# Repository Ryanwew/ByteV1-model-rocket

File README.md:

This repo contains all of the design files I used to create an arduino-based flight computer and groud control system.

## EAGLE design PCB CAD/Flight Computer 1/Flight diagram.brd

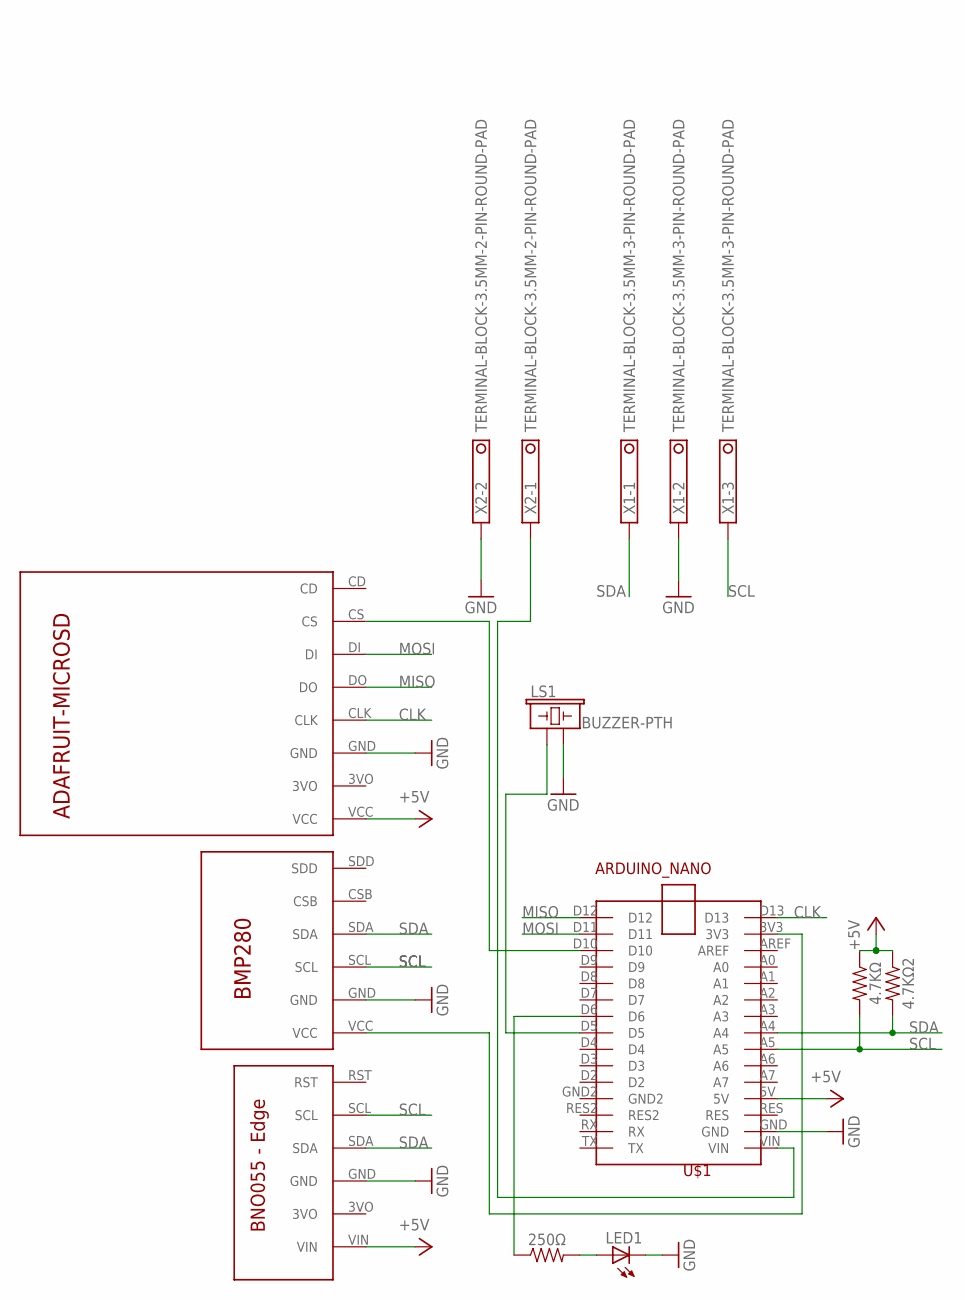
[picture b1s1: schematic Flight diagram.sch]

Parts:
4.7KΩ, 4.7KΩ2, 250Ω: AXIAL-0.3
LED1: LED5MM
LS1: BUZZER-PTH; BUZZER-12MM
U$1: ARDUINO_NANO; ARDUIN_NANO
U$2: BNO055
U$3: ADAFRUIT-MICROSD
U$4: BMP280
X1: TERMINAL-BLOCK-3.5MM-3-PIN-ROUND-PAD; TERMINAL-BLOCK-3-PIN-3.5MM-ROUND-PAD
X2: TERMINAL-BLOCK-3.5MM-2-PIN-ROUND-PAD; TERMINAL-BLOCK-2-PIN-3.5MM-ROUND-PAD

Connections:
+5V: 4.7KΩ.P$1 (1), 4.7KΩ2.P$1 (1), U$1.5V, U$2.VIN, U$3.VCC
CLK: U$1.D13, U$3.CLK
GND: LED1.K (C), LS1.- (2), U$1.GND, U$2.GND, U$3.GND, U$4.GND, X1.2, X2.2
MISO: U$1.D12, U$3.DO
MOSI: U$1.D11, U$3.DI
unnamed: 250Ω.P$2 (2), LED1.A
unnamed: U$1.3V3, U$4.VCC
unnamed: U$1.VIN, X2.1
unnamed: 250Ω.P$1 (1), U$1.D6
unnamed: U$1.D10, U$3.CS
unnamed: LS1.+ (1), U$1.D5
SCL: 4.7KΩ.P$2 (2), U$1.A5, U$2.SCL, U$4.SCL, X1.3
SDA: 4.7KΩ2.P$2 (2), U$1.A4, U$2.SDA, U$4.SDA, X1.1

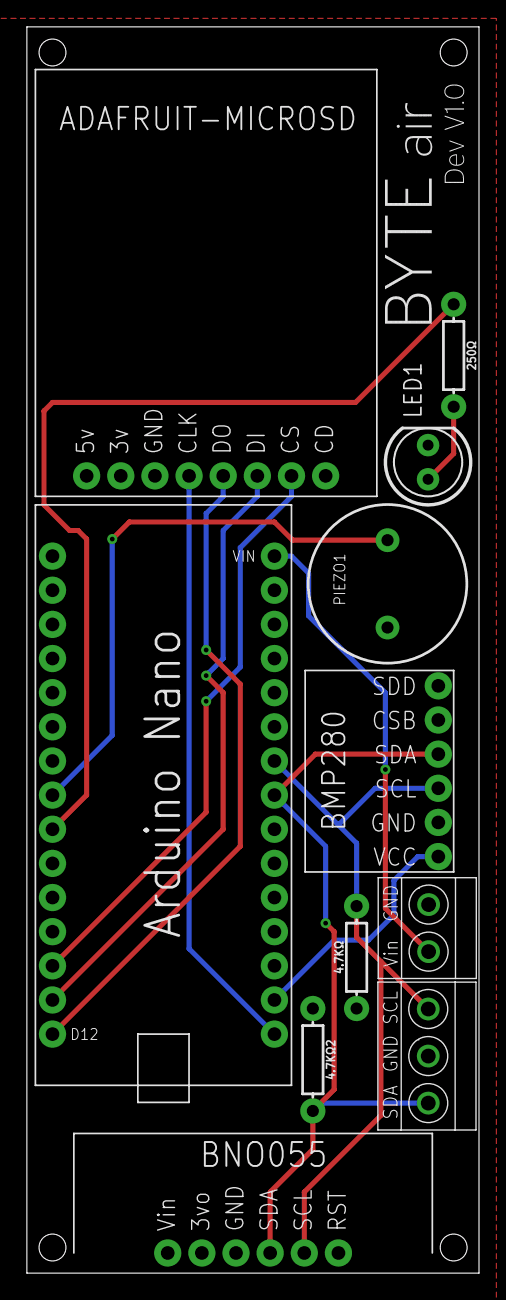
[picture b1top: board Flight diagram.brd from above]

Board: 2 copper layers, 33.6 x 92.7 mm, 11 parts (0 on the bottom side), 13 nets.

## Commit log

2020-06-25 First files
    2 initial testing files
2020-06-27 EAGLE Devices
    Arduino is premade, BNO is a custom-designed simplified library.
2020-06-27 New library
    Custom RoboJax BMP280 EAGLE library
2020-06-27 New library
    Custom simplified library for Aadafruit microSD breakout.
2020-06-29 Edge BNO055
    Version of BNO055 that sits on the edge of the PCB
2020-12-20 Added PCB CAD
2020-12-21 Removed Excess Files
2021-01-17 Added BoM and photo
2021-03-29 Code Re-distribution
2021-03-31 Serial rocket to station communication, added "capture" command
2021-03-31 adding i2c check, added bluetooth validation for GS
2021-04-01 File division
2021-04-02 Shift Register using OOP
2021-04-02 Redid control code with OOP
2021-04-03 code sync
2021-04-03 Program Variations
2021-04-04 MVC Attained
2021-04-04 Byte overflow error fixed, system working
2021-04-06 Serial data validation, file shifting
2021-04-06 Data validation testing
2021-04-06 Validation issue fixed
2021-04-07 Station OOP
2021-04-11 StationOOP proto finished
2021-04-11 OR error management
2021-04-14 Station OOP MVC search
2021-04-15 Returning to original station I2C
2021-04-16 Fixing I2c bus
2021-04-23 I2c error fixed, StationOOP working
2021-04-24 SD testing
2021-04-26 Begun SD conversion to binary files
2021-04-27 floating point testing
2021-04-27 Added .dat evaluation
2021-04-27 Multibyte parsing
2021-04-27 CSV export
2021-04-27 Finished test parse app
2021-04-27 Remade URP for serialized data
2021-04-28 BNO isolation
2021-04-28 Revised isolated BMP
2021-04-28 isolated BMP written
2021-04-30 Started RocketOOP
2021-05-01 Base RocketOOP
2021-05-02 Transferring sensor actions to function
2021-05-08 Finished RocketOOP first prototype
2021-05-16 RocketOOP troubleshooting
2021-05-16 Corrected full loop failure
2021-05-17 data conversion gui
2021-05-17 GUI Implemented for data conversion
2021-05-17 reformatted converter for RocketOOP
2021-05-18 added simulation
2021-05-19 Created fairing, improved simulation
2021-05-20 Updated fairing
2021-05-22 Begun station schematic
2021-05-26 shift issue isolated
2021-05-27 Fixing serial state issues
2021-05-28 debugging shift class
2021-05-28 fixed shift register issues, added continuity detection to station
2021-05-30 12v boost circuit
2021-06-05 Power circuit finished
2021-06-08 Ground Station schematic first pass finished
2021-06-09 Redid library management
2021-06-12 Footprint layout
2021-06-15 drc validation
2021-06-16 Added Logos
2021-06-17 PCB design freeze, component redesign
2021-06-21 major component redesign
2021-06-24 Finished BoM
2021-07-02 DRC 1
2021-07-02 design review 1
2021-07-05 ground system conversion
2021-07-10 First GS revision ordered
2021-07-11 update revisions
2021-07-13 Final board ouput
2021-07-13 Paused edits
2021-07-17 Control schematic development
    NOTE: First push after beginning control, check previous iteration for 100% clean station ecad
2022-01-19 Readme reformatting

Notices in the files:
parts and their libraries:
SparkFun-Resistors: Licensing: Creative Commons ShareAlike 4.0 International - https://creativecommons.org/licenses/by-sa/4.0
